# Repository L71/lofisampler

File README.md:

LoFi sampler / filter / dist module
===================================

This is a Eurorack module built upon the circuits described here: 

http://www.bastl-instruments.com/instruments/omsynth/omsynthvideo3/
http://www.bastl-instruments.com/instruments/omsynth/omsynthvideo3/lo-fi-vcf/

The added stuff here is Eurorack power supply circuits, an output amplifier and
some circuitry to get correct polarity on the sample rate/filter bandwidth control voltage.

It does sample and play stuff back but it's _really_ lofi as a sampler, lots of clicks at
start and stop of playback. It works better as a lofi filter or dist.

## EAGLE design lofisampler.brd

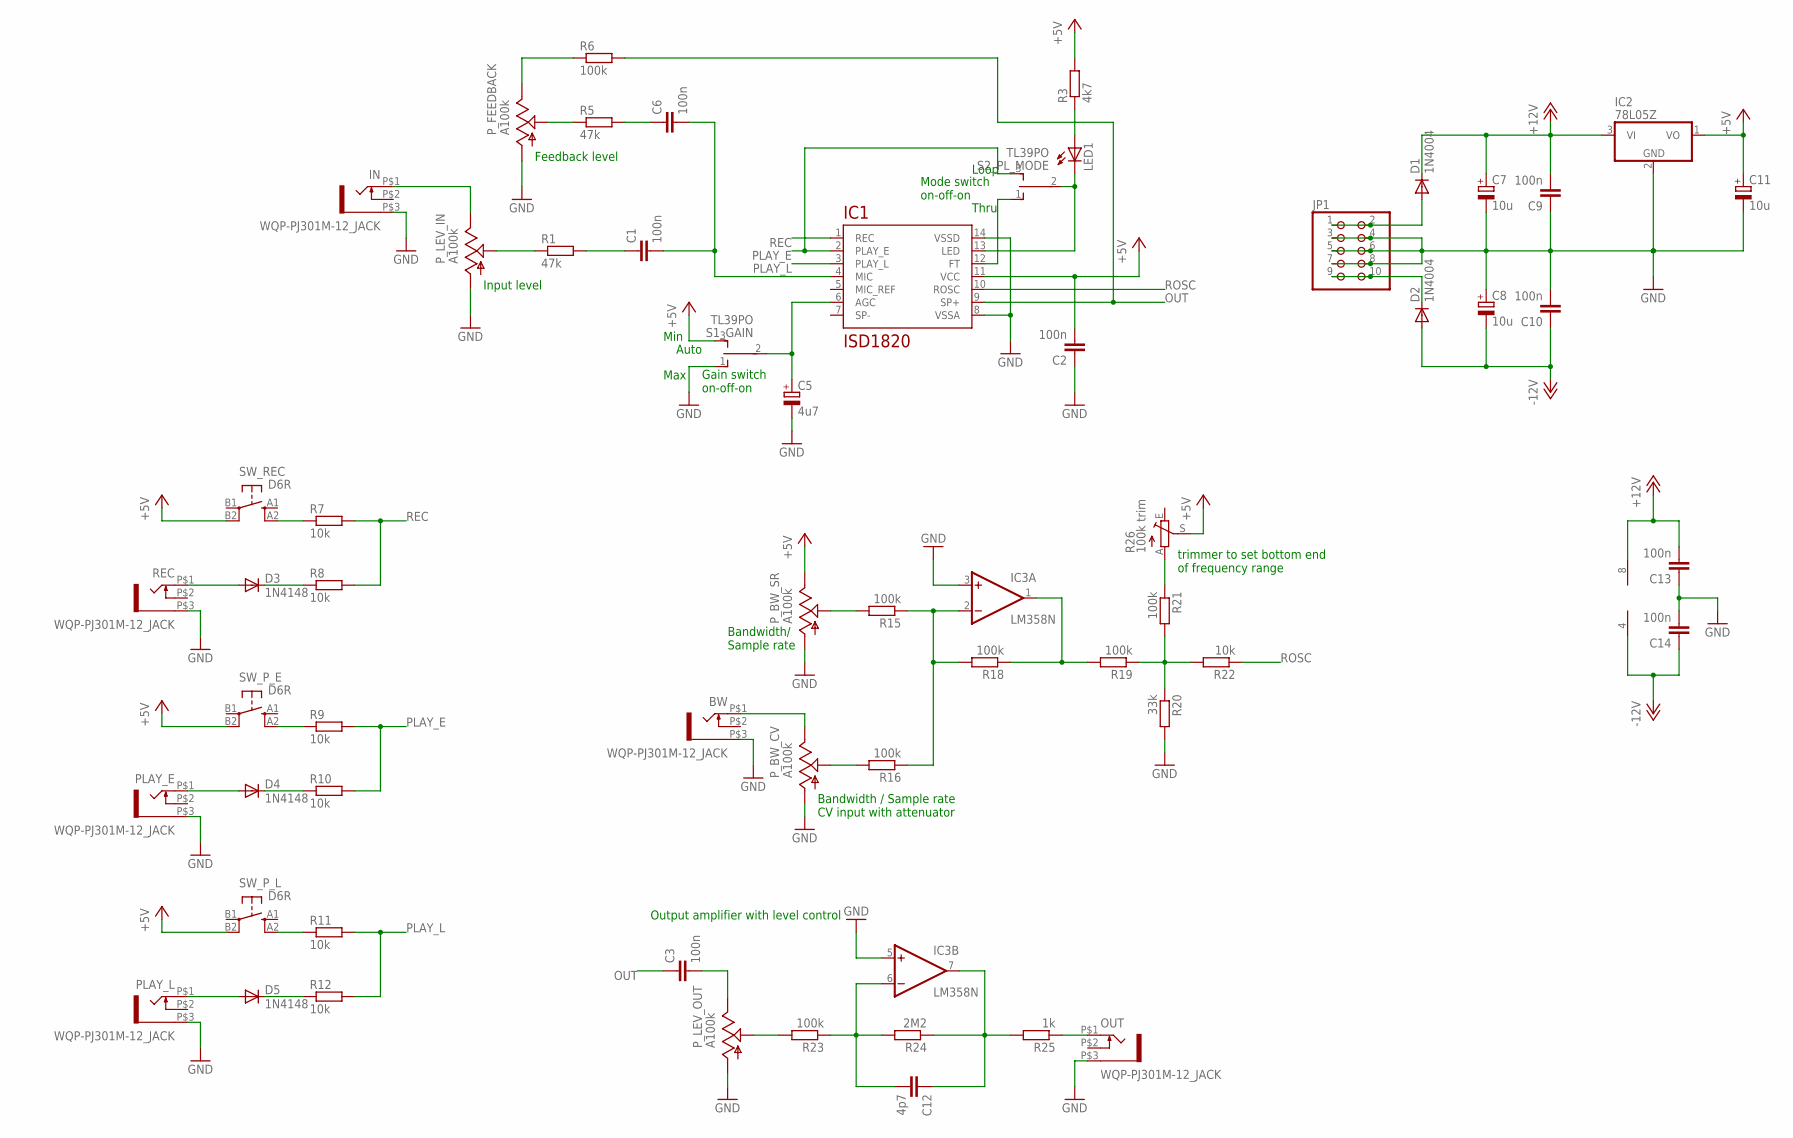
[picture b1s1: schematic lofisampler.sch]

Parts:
BW: WQP-PJ301M-12_JACK
C1, C3, C6: 100n; C050-025X075
C2, C9, C10, C13, C14: 100n; C025-025X050
C5: 4u7; E2,5-5
C7, C8, C11: 10u; E2,5-5
C12: 4p7; C025-025X050
D1, D2: 1N4004; DO41-10
D3, D4, D5: 1N4148; DO35-7
IC1: ISD1820; DIL14
IC2: 78L05Z; TO92
IC3: LM358N; DIL08
IN: WQP-PJ301M-12_JACK
JP1: PINHD-2X5; 2X05
LED1: LED5MM
OUT: WQP-PJ301M-12_JACK
PLAY_E: WQP-PJ301M-12_JACK
PLAY_L: WQP-PJ301M-12_JACK
P_BW_CV: A100k; ALPS_POT_VERTICAL
P_BW_SR: A100k; ALPS_POT_VERTICAL
P_FEEDBACK: A100k; ALPS_POT_VERTICAL
P_LEV_IN: A100k; ALPS_POT_VERTICAL
P_LEV_OUT: A100k; ALPS_POT_VERTICAL
R1, R5: 47k; 0207/2V
R3: 4k7; 0207/2V
R6, R15, R16, R18, R19, R21, R23: 100k; 0207/2V
R7, R8, R9, R10, R11, R12, R22: 10k; 0207/2V
R20: 33k; 0207/2V
R24: 2M2; 0207/2V
R25: 1k; 0207/2V
R26: 100k trim; B25P
REC: WQP-PJ301M-12_JACK
S1_GAIN, S2_PL_MODE: TL39PO; TL3XPO
SW_P_E: D6R
SW_P_L: D6R
SW_REC: D6R

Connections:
+5V: C2.2, C11.+, IC1.11 (VCC), IC2.1 (VO), P_BW_SR.P$1 (E), R3.2, R26.S, S1_GAIN.3 (S), SW_P_E.B2 (P1), SW_P_L.B2 (P1), SW_REC.B2 (P1)
+12V: C7.+, C9.2, C13.2, D1.C, IC2.3 (VI), IC3.8 (V+)
-12V: C8.-, C10.1, C14.1, D2.A, IC3.4 (V-)
GND: BW.P$3 (1), C2.1, C5.-, C7.-, C8.+, C9.1, C10.2, C11.-, C13.1, C14.2, IC1.8 (VSSA), IC1.14 (VSSD), IC2.2 (GND), IC3.3 (+IN), IC3.5 (+IN), IN.P$3 (1), JP1.3, JP1.4, JP1.5, JP1.6, JP1.7, JP1.8, OUT.P$3 (1), PLAY_E.P$3 (1), PLAY_L.P$3 (1), P_BW_CV.P$3 (A), P_BW_SR.P$3 (A), P_FEEDBACK.P$3 (A), P_LEV_IN.P$3 (A), P_LEV_OUT.P$3 (A), R20.2, REC.P$3 (1), S1_GAIN.1 (O)
unnamed: IN.P$1 (2), P_LEV_IN.P$1 (E)
unnamed: P_LEV_IN.P$2 (S), R1.1
unnamed: C1.1, R1.2
unnamed: C1.2, C6.2, IC1.4 (MIC)
unnamed: LED1.A, R3.1
unnamed: IC1.13 (LED), LED1.K (C), S2_PL_MODE.2
unnamed: IC1.12 (FT), S2_PL_MODE.1 (O)
unnamed: P_FEEDBACK.P$1 (E), R6.1
unnamed: D1.A, JP1.1, JP1.2
unnamed: P_FEEDBACK.P$2 (S), R5.1
unnamed: C5.+, IC1.6 (AGC), S1_GAIN.2
unnamed: C6.1, R5.2
unnamed: D2.C, JP1.9, JP1.10
unnamed: R21.1, R26.A
unnamed: C3.2, P_LEV_OUT.P$1 (E)
unnamed: P_LEV_OUT.P$2 (S), R23.2
unnamed: C12.2, IC3.6 (-IN), R23.1, R24.2
unnamed: D3.A, REC.P$1 (2)
unnamed: D3.C, R8.1
unnamed: P_BW_SR.P$2 (S), R15.2
unnamed: R7.1, SW_REC.A2 (S1)
unnamed: P_BW_CV.P$2 (S), R16.2
unnamed: D4.A, PLAY_E.P$1 (2)
unnamed: D4.C, R10.1
unnamed: IC3.2 (-IN), R15.1, R16.1, R18.2
unnamed: R9.1, SW_P_E.A2 (S1)
unnamed: D5.A, PLAY_L.P$1 (2)
unnamed: D5.C, R12.1
unnamed: C12.1, IC3.7 (OUT), R24.1, R25.2
unnamed: R11.1, SW_P_L.A2 (S1)
unnamed: IC3.1 (OUT), R18.1, R19.2
unnamed: BW.P$1 (2), P_BW_CV.P$1 (E)
unnamed: R19.1, R20.1, R21.2, R22.2
unnamed: OUT.P$1 (2), R25.1
OUT: C3.1, IC1.9 (SP+), R6.2
PLAY_E: IC1.2 (PLAY_E), R9.2, R10.2, S2_PL_MODE.3 (S)
PLAY_L: IC1.3 (PLAY_L), R11.2, R12.2
REC: IC1.1 (REC), R7.2, R8.2
ROSC: IC1.10 (ROSC), R22.1

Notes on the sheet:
Loop
Thru
Max
Min
Auto
Input level
Feedback level
Gain switch on-off-on
Mode switch on-off-on
Bandwidth/ Sample rate
Bandwidth / Sample rate CV input with attenuator
Output amplifier with level control
trimmer to set bottom end of frequency range

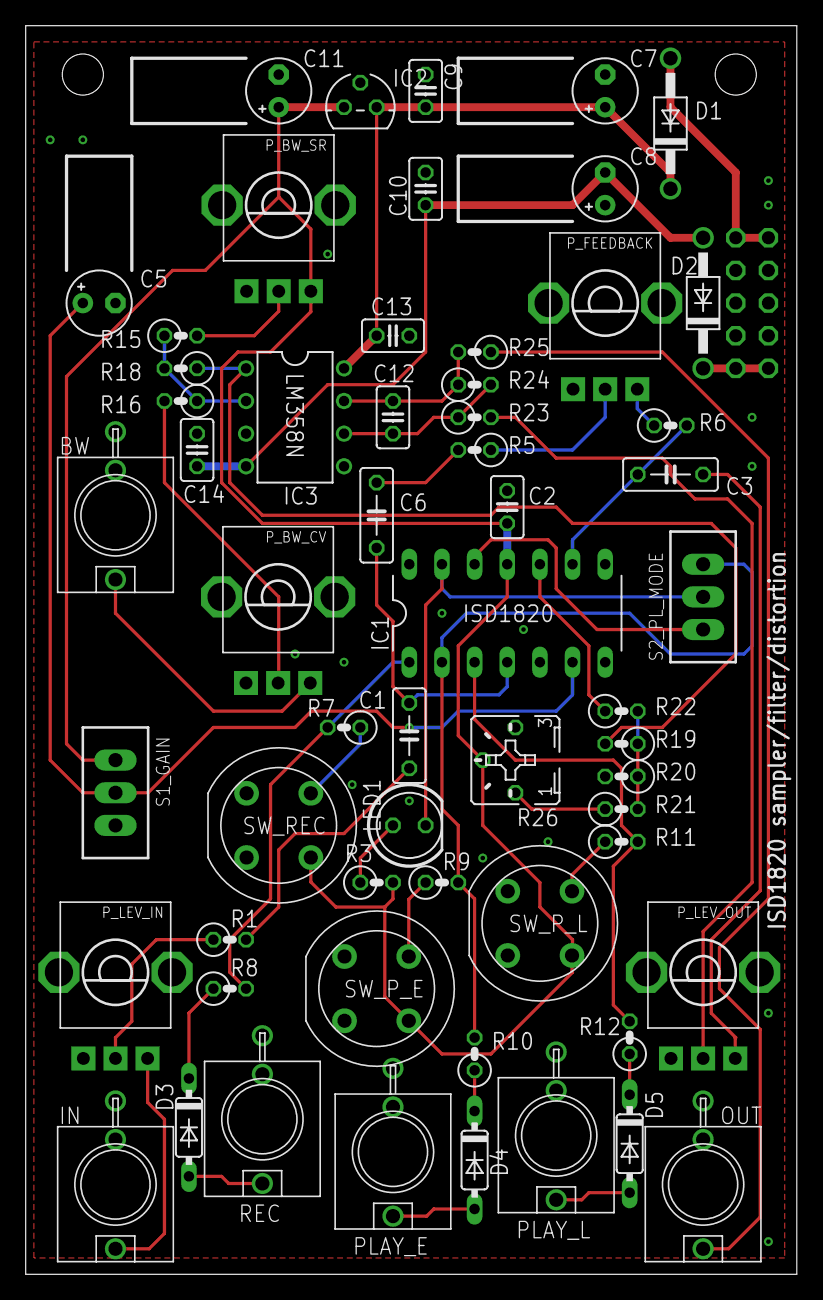
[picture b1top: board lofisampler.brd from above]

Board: 2 copper layers, 60.0 x 97.1 mm, 60 parts (1 on the bottom side), 43 nets.

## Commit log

2018-05-30 Initial commit. First ordered prototype version.
2018-06-07 Changed current limit resistors for the push buttons to 10k. Using 47k seems to deliver too small a current sometimes (some chips do not trigger on this).
2018-06-07 Adding README.
2022-02-27 latest updates
2022-02-27 updated.
2022-02-27 picture added.

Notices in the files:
lofisampler.brd:
cc-by-sa 2018
